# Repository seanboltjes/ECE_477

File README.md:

# Swing Analysis (Team 13)
Swing Analyzer's code repo!

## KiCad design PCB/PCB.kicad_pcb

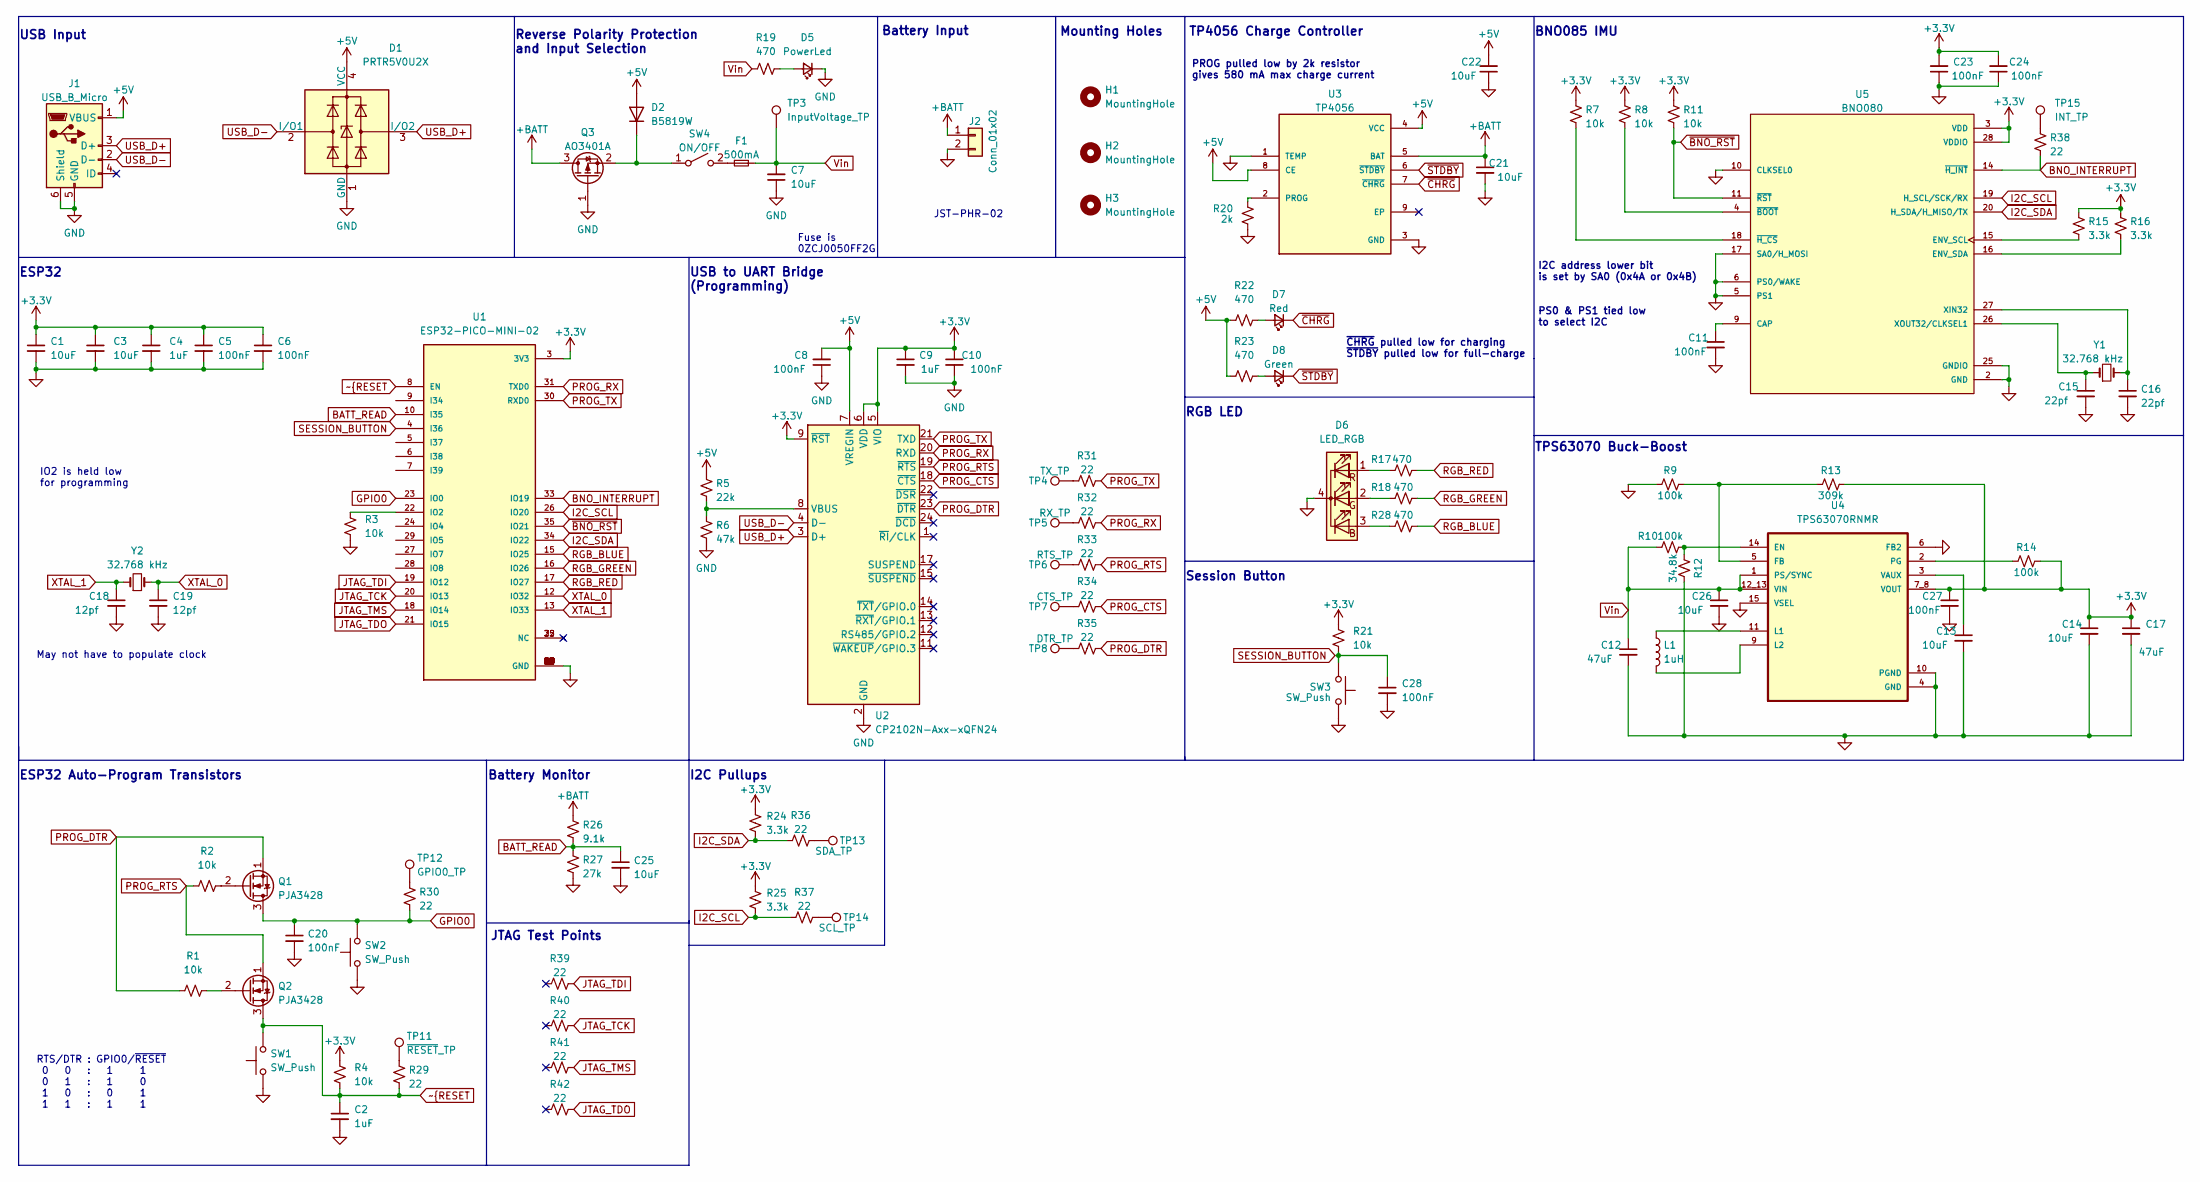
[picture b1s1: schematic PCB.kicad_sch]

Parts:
C1, C3, C13, C14, C25, C26: 10uF; C_0603_1608Metric
C2, C4, C9: 1uF; C_0603_1608Metric
C5, C6, C8, C10, C11, C20, C23, C24, C27, C28: 100nF; C_0603_1608Metric
C7, C21, C22: 10uF; C_1206_3216Metric
C12: 47uF; C_1206_3216Metric_Pad1.33x1.80mm_HandSolder
C15, C16: 22pf; C_0603_1608Metric
C17: 47uF; C_1206_3216Metric
C18, C19: 12pf; C_0603_1608Metric
D1: PRTR5V0U2X; SOT-143
D2: B5819W; D_1206_3216Metric
D5: PowerLed; LED_0805_2012Metric_Pad1.15x1.40mm_HandSolder
D6: LED_RGB; LED_D5.0mm-4_RGB
D7: Red; LED_0805_2012Metric_Pad1.15x1.40mm_HandSolder
D8: Green; LED_0805_2012Metric_Pad1.15x1.40mm_HandSolder
F1: 500mA; RESC3216X125N
H1, H2, H3: MountingHole; MountingHole_2.2mm_M2_Pad_Via
J1: USB_B_Micro; USB_Micro-B_Molex_47346-0001
J2: Conn_01x02; JST_PHR-2
L1: 1uH; IHLP1212BZER1R0M11
Q1, Q2: PJA3428; SC-82AA_Handsoldering
Q3: AO3401A; SOT-23
R1, R2, R3, R4, R7, R8, R11, R21: 10k; R_0603_1608Metric
R5: 22k; R_0603_1608Metric
R6: 47k; R_0603_1608Metric
R9, R10, R14: 100k; R_0603_1608Metric
R12: 34.8k; R_0603_1608Metric
R13: 309k; R_0603_1608Metric
R15, R16, R24, R25: 3.3k; R_0603_1608Metric
R17, R18, R19, R22, R23, R28: 470; R_0603_1608Metric
R20: 2k; R_0603_1608Metric
R26: 9.1k; R_0603_1608Metric
R27: 27k; R_0603_1608Metric
R29, R30, R31, R32, R33, R34, R35, R36, R37, R38, R39, R40, R41, R42: 22; R_0603_1608Metric
SW1, SW2: SW_Push; SW_Push_1P1T_NO_Vertical_Wuerth_434133025816
SW3: SW_Push; SW_Tactile_SPST_Angled_PTS645Vx58-2LFS
SW4: ON/OFF; CUS-12TB
TP3: InputVoltage_TP; TestPoint_Pad_D1.0mm
TP4: TX_TP; TestPoint_Pad_D1.0mm
TP5: RX_TP; TestPoint_Pad_D1.0mm
TP6: RTS_TP; TestPoint_Pad_D1.0mm
TP7: CTS_TP; TestPoint_Pad_D1.0mm
TP8: DTR_TP; TestPoint_Pad_D1.0mm
TP11: ~{RESET}_TP; TestPoint_Pad_D1.0mm
TP12: GPIO0_TP; TestPoint_Pad_D1.0mm
TP13: SDA_TP; TestPoint_Pad_D1.0mm
TP14: SCL_TP; TestPoint_Pad_D1.0mm
TP15: INT_TP; TestPoint_Pad_D1.0mm
U1: ESP32-PICO-MINI-02; MODULE_ESP32-PICO-MINI-02; PARTREV v1.0
U2: CP2102N-Axx-xQFN24; QFN-24-1EP_4x4mm_P0.5mm_EP2.6x2.6mm
U3: TP4056; SOP127P600X175-9N
U4: TPS63070RNMR; VREG_TPS63070RNMR
U5: BNO080; IC_BNO080; PARTREV 1.6
Y1, Y2: 32.768 kHz; Crystal_SMD_EuroQuartz_EQ161-2Pin_3.2x1.5mm

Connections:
+3.3V: C1.1, C3.1, C4.1, C5.1, C6.1, C9.1, C10.1, C14.1, C17.1, C23.2, C24.2, C27.1, R4.1, R7.1, R8.1, R11.1, R13.1, R14.1, R15.1, R16.1, R21.1, R24.1, R25.1, U1.3 (3V3), U2.5 (VIO), U2.6 (VDD), U2.9 (~RST), U4.7_8 (VOUT), U5.3 (VDD), U5.28 (VDDIO)
+5V: C8.2, C22.2, D1.4 (VCC), D2.2 (A), J1.1 (VBUS), R5.1, R22.1, R23.1, U2.7 (VREGIN), U3.4 (VCC), U3.8 (CE)
+BATT: C21.1, J2.1, Q3.3 (D), R26.1, U3.5 (BAT)
BATT_READ: C25.1, R26.2, R27.1, U1.10 (I35)
BNO_INTERRUPT: R38.1, U1.33 (IO19), U5.14 (~H_INT)
GND: C1.2, C2.2, C3.2, C4.2, C5.2, C6.2, C7.1, C8.1, C9.2, C10.2, C11.2, C12.2, C13.2, C14.2, C15.2, C16.2, C17.2, C18.2, C19.2, C20.2, C21.2, C22.1, C23.1, C24.1, C25.2, C26.2, C27.2, C28.2, D1.1 (GND), D5.1 (K), D6.4 (K), J1.5 (GND), J1.6 (Shield), J2.2, Q3.1 (G), R3.1, R6.2, R9.2, R12.1, R20.1, R27.2, SW1.1, SW2.1, SW3.2, U1.1 (GND), U1.2 (GND), U1.11 (GND), U1.14 (GND), U1.36 (GND), U1.37 (GND), U1.38 (GND), U1.39 (GND), U1.40 (GND), U1.41 (GND), U1.42 (GND), U1.43 (GND), U1.44 (GND), U1.45 (GND), U1.46 (GND), U1.47 (GND), U1.48 (GND), U1.49 (GND), U1.50 (GND), U1.51 (GND), U1.52 (GND), U1.53 (GND), U1.54 (GND), U1.55 (GND), U1.56 (GND), U1.57 (GND), U1.58 (GND), U1.59 (GND), U1.60 (GND), U1.61 (GND), U2.2 (GND), U2.25 (GND), U3.1 (TEMP), U3.3 (GND), U4.4 (GND), U4.6 (FB2), U4.10 (PGND), U4.15 (VSEL), U5.2 (GND), U5.5 (PS1), U5.6 (PS0/WAKE), U5.10 (CLKSEL0), U5.17 (SA0/H_MOSI), U5.25 (GNDIO)
GPIO0: C20.1, Q1.3 (D), R30.2, SW2.2, U1.23 (IO0)
I2C_SCL: R25.2, R37.1, U1.26 (IO20), U5.19 (H_SCL/SCK/RX)
I2C_SDA: R24.2, R36.1, U1.34 (IO22), U5.20 (H_SDA/H_MISO/TX)
JTAG_TCK: R40.2, U1.20 (IO13)
JTAG_TDI: R39.2, U1.19 (IO12)
JTAG_TDO: R42.2, U1.21 (IO15)
JTAG_TMS: R41.2, U1.18 (IO14)
unnamed: C11.1, U5.9 (CAP)
unnamed: C13.1, U4.3 (VAUX)
unnamed: C15.1, U5.26 (XOUT32/CLKSEL1), Y1.1
unnamed: C16.1, U5.27 (XIN32), Y1.2
unnamed: D2.1 (K), Q3.2 (S), SW4.1 (A)
unnamed: D5.2 (A), R19.2
unnamed: D6.1 (RA), R17.1
unnamed: D6.2 (GA), R18.1
unnamed: D6.3 (BA), R28.1
unnamed: D7.2 (A), R22.2
unnamed: D8.2 (A), R23.2
unnamed: F1.1, SW4.2 (B)
unnamed: L1.1, U4.11 (L1)
unnamed: L1.2, U4.9 (L2)
unnamed: Q1.2 (G), R2.2
unnamed: Q2.2 (G), R1.2
unnamed: R3.2, U1.22 (IO2)
unnamed: R5.2, R6.1, U2.8 (VBUS)
unnamed: R7.2, U5.18 (~H_CS)
unnamed: R8.2, U5.4 (~BOOT)
unnamed: R10.2, R12.2, U4.14 (EN)
unnamed: R9.1, R13.2, U4.5 (FB)
unnamed: R14.2, U4.2 (PG)
unnamed: R15.2, U5.15 (ENV_SCL)
unnamed: R16.2, U5.16 (ENV_SDA)
unnamed: R20.2, U3.2 (PROG)
unnamed: R29.1, TP11.1
unnamed: R30.1, TP12.1
unnamed: R31.1, TP4.1
unnamed: R32.1, TP5.1
unnamed: R33.1, TP6.1
unnamed: R34.1, TP7.1
unnamed: R35.1, TP8.1
unnamed: R36.2, TP13.1
unnamed: R37.2, TP14.1
unnamed: R38.2, TP15.1
PROG_CTS: R34.2, U2.18 (~CTS)
PROG_DTR: Q1.1 (S), R1.1, R35.2, U2.23 (~DTR)
PROG_RTS: Q2.1 (S), R2.1, R33.2, U2.19 (~RTS)
PROG_RX: R32.2, U1.31 (TXD0), U2.20 (RXD)
PROG_TX: R31.2, U1.30 (RXD0), U2.21 (TXD)
RGB_BLUE: R28.2, U1.15 (IO25)
RGB_GREEN: R18.2, U1.16 (IO26)
RGB_RED: R17.2, U1.17 (IO27)
SESSION_BUTTON: C28.1, R21.2, SW3.1, U1.4 (I36)
USB_D+: D1.3 (I/O2), J1.3 (D+), U2.3 (D+)
USB_D-: D1.2 (I/O1), J1.2 (D-), U2.4 (D-)
Vin: C7.2, C12.1, C26.1, F1.2, R10.1, R19.1, TP3.1, U4.1 (PS/SYNC), U4.12_13 (VIN)
XTAL_0: C19.1, U1.12 (IO32), Y2.2
XTAL_1: C18.1, U1.13 (IO33), Y2.1
~BNO_RST: R11.2, U1.35 (IO21), U5.11 (~RST)
~CHRG: D7.1 (K), U3.7 (~CHRG)
~RESET: C2.1, Q2.3 (D), R4.2, R29.2, SW1.2, U1.8 (EN)
~STDBY: D8.1 (K), U3.6 (~STDBY)

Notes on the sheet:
RTS/DTR : GPIO0/~{RESET} 0 0 : 1 1 0 1 : 1 0 1 0 : 0 1 1 1 : 1 1
PROG pulled low by 2k resistor gives 580 mA max charge current
May not have to populate clock
BNO085 IMU
USB Input
ESP32
IO2 is held low for programming
Mounting Holes
Reverse Polarity Protection and Input Selection
JST-PHR-02
I2C address lower bit is set by SA0 (0x4A or 0x4B)
Fuse is 0ZCJ0050FF2G
Battery Monitor
USB to UART Bridge (Programming)
JTAG Test Points
I2C Pullups
Session Button
~{CHRG} pulled low for charging ~{STDBY} pulled low for full-charge
ESP32 Auto-Program Transistors
RGB LED
Battery Input
PS0 & PS1 tied low to select I2C
TP4056 Charge Controller
TPS63070 Buck-Boost

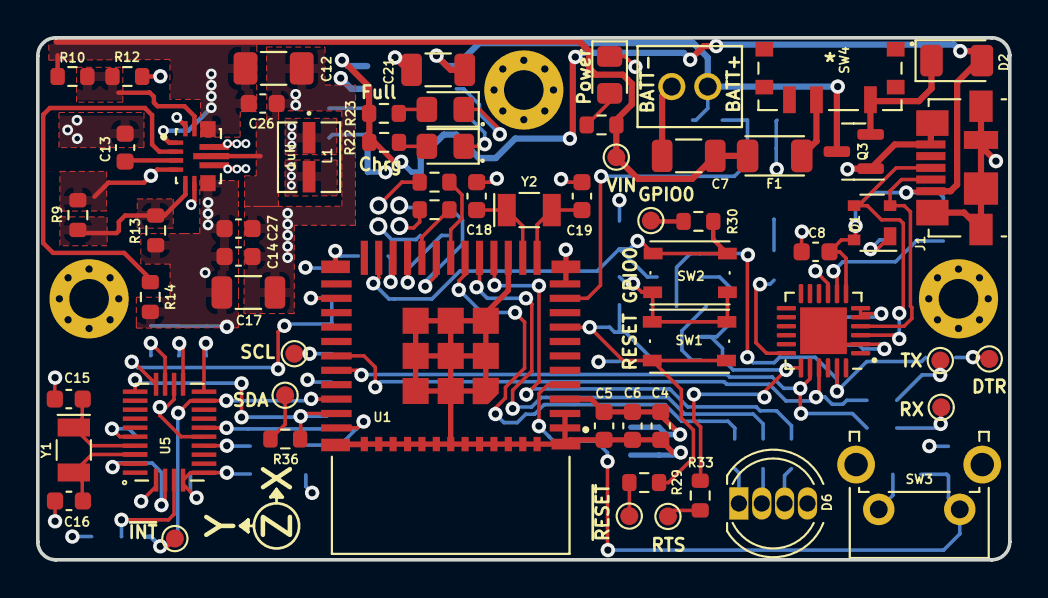
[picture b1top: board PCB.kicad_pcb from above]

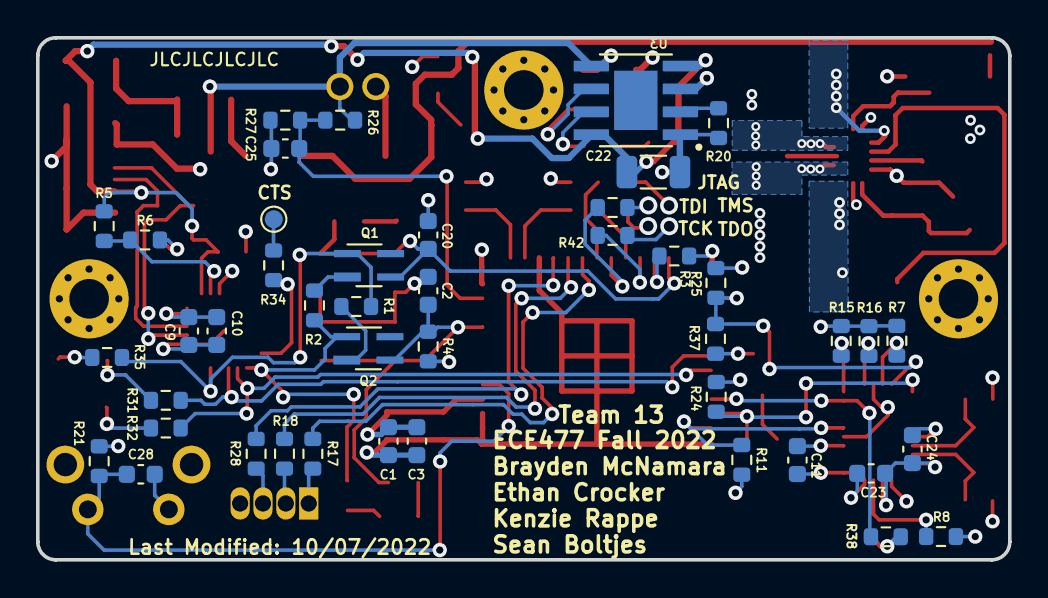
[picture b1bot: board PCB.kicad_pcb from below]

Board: 4 copper layers, 54.0 x 29.0 mm, 108 parts (44 on the bottom side), 67 nets.

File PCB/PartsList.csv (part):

Source:,C:\Users\seanb\Downloads\PCB-Team13\PCB-Team13\PCB.kicad_sch,,,,,,,,,
Date:,10/17/2022 13:33,,,,,,,,,
Tool:,Eeschema (6.0.7),,,,,,,,,
Generator:,C:\Program Files\KiCad\6.0\bin\scripting\plugins/bom_csv_grouped_by_value.py,,,,,,,,,
Component Count:,108,,,,,,,,,
,,,,,,,,,,
Individual Components:,,,,,,,,,,
,,,,,,,,,,
Item,Qty,Reference(s),Value,LibPart,Footprint,Datasheet,MANUFACTURER,MAXIMUM_PACKAGE_HEIGHT,PARTREV,STANDARD
,,C1,10uF,Device:C_Small,Capacitor_SMD:C_0603_1608Metric,~,,,,
,,C2,1uF,Device:C_Small,Capacitor_SMD:C_0603_1608Metric,~,,,,
,,C3,10uF,Device:C_Small,Capacitor_SMD:C_0603_1608Metric,~,,,,
,,C4,1uF,Device:C_Small,Capacitor_SMD:C_0603_1608Metric,~,,,,
,,C5,100nF,Device:C_Small,Capacitor_SMD:C_0603_1608Metric,~,,,,
,,C6,100nF,Device:C_Small,Capacitor_SMD:C_0603_1608Metric,~,,,,
,,C7,10uF,Device:C_Small,Capacitor_SMD:C_1206_3216Metric,~,,,,
,,C8,100nF,Device:C_Small,Capacitor_SMD:C_0603_1608Metric,~,,,,
,,C9,1uF,Device:C_Small,Capacitor_SMD:C_0603_1608Metric,~,,,,
,,C10,100nF,Device:C_Small,Capacitor_SMD:C_0603_1608Metric,~,,,,
,,C11,100nF,Device:C_Small,Capacitor_SMD:C_0603_1608Metric,~,,,,
,,C12,47uF,Device:C_Small,Capacitor_SMD:C_1206_3216Metric_Pad1.33x1.80mm_HandSolder,~,,,,
,,C13,10uF,Device:C_Small,Capacitor_SMD:C_0603_1608Metric,~,,,,
,,C14,10uF,Device:C_Small,Capacitor_SMD:C_0603_1608Metric,~,,,,
,,C15,12pf,Device:C_Small,Capacitor_SMD:C_0603_1608Metric,~,,,,
,,C16,12pf,Device:C_Small,Capacitor_SMD:C_0603_1608Metric,~,,,,
,,C17,47uF,Device:C_Small,Capacitor_SMD:C_1206_3216Metric,~,,,,
,,C18,12pf,Device:C_Small,Capacitor_SMD:C_0603_1608Metric,~,,,,
,,C19,12pf,Device:C_Small,Capacitor_SMD:C_0603_1608Metric,~,,,,
,,C20,100nF,Device:C_Small,Capacitor_SMD:C_0603_1608Metric,~,,,,
,,C21,10uF,Device:C_Small,Capacitor_SMD:C_1206_3216Metric,~,,,,
,,C22,10uF,Device:C_Small,Capacitor_SMD:C_1206_3216Metric,~,,,,
,,C23,100nF,Device:C_Small,Capacitor_SMD:C_0603_1608Metric,~,,,,
,,C24,100nF,Device:C_Small,Capacitor_SMD:C_0603_1608Metric,~,,,,
,,C25,10uF,Device:C_Small,Capacitor_SMD:C_0603_1608Metric,~,,,,
,,C26,10uF,Device:C_Small,Capacitor_SMD:C_0603_1608Metric,~,,,,
,,C27,100nF,Device:C_Small,Capacitor_SMD:C_0603_1608Metric,~,,,,
,,C28,100nF,Device:C_Small,Capacitor_SMD:C_0603_1608Metric,~,,,,
,,D1,PRTR5V0U2X,Power_Protection:PRTR5V0U2X,Package_TO_SOT_SMD:SOT-143,https://assets.nexperia.com/documents/data-sheet/PRTR5V0U2X.pdf,,,,
,,D2,1N4148,Diode:1N4148,Diode_SMD:D_1206_3216Metric,https://assets.nexperia.com/documents/data-sheet/1N4148_1N4448.pdf,,,,
,,D5,PowerLed,Device:LED_Small,LED_SMD:LED_0805_2012Metric_Pad1.15x1.40mm_HandSolder,~,,,,
,,D6,LED_RGB,Device:LED_RGBK,LED_THT:LED_D5.0mm-4_RGB,~,,,,
,,D7,Red,Device:LED_Small,LED_SMD:LED_0805_2012Metric_Pad1.15x1.40mm_HandSolder,~,,,,
,,D8,Green,Device:LED_Small,LED_SMD:LED_0805_2012Metric_Pad1.15x1.40mm_HandSolder,~,,,,
,,F1,500mA,Device:Fuse_Small,0ZCJ0050FF2G:RESC3216X125N,~,,,,
,,H1,MountingHole,Mechanical:MountingHole,MountingHole:MountingHole_2.2mm_M2_Pad_Via,~,,,,
,,H2,MountingHole,Mechanical:MountingHole,MountingHole:MountingHole_2.2mm_M2_Pad_Via,~,,,,
,,H3,MountingHole,Mechanical:MountingHole,MountingHole:MountingHole_2.2mm_M2_Pad_Via,~,,,,
,,J1,USB_B_Micro,Connector:USB_B_Micro,Connector_USB:USB_Micro-B_Molex_47346-0001,~,,,,
,,J2,Conn_01x02,Connector_Generic:Conn_01x02,PHR-2:JST_PHR-2,~,,,,
,,L1,L,Device:L,inductor:IHLP1212BZERR56M11,~,,,,
,,Q1,PJA3428,Transistor_FET:2N7000,Package_TO_SOT_SMD:SC-82AA_Handsoldering,https://www.vishay.com/docs/70226/70226.pdf,,,,
,,Q2,PJA3428,Transistor_FET:2N7000,Package_TO_SOT_SMD:SC-82AA_Handsoldering,https://www.vishay.com/docs/70226/70226.pdf,,,,
,,Q3,AO3401A,Transistor_FET:AO3401A,Package_TO_SOT_SMD:SOT-23,http://www.aosmd.com/pdfs/datasheet/AO3401A.pdf,,,,
,,R1,10k,Device:R_Small_US,Resistor_SMD:R_0603_1608Metric,~,,,,
,,R2,10k,Device:R_Small_US,Resistor_SMD:R_0603_1608Metric,~,,,,
,,R3,10k,Device:R_Small_US,Resistor_SMD:R_0603_1608Metric,~,,,,
,,R4,10k,Device:R_Small_US,Resistor_SMD:R_0603_1608Metric,~,,,,
,,R5,22k,Device:R_Small_US,Resistor_SMD:R_0603_1608Metric,~,,,,
,,R6,47k,Device:R_Small_US,Resistor_SMD:R_0603_1608Metric,~,,,,
,,R7,10k,Device:R_Small_US,Resistor_SMD:R_0603_1608Metric,~,,,,
,,R8,10k,Device:R_Small_US,Resistor_SMD:R_0603_1608Metric,~,,,,
,,R9,100k,Device:R_Small_US,Resistor_SMD:R_0603_1608Metric,~,,,,
,,R10,100k,Device:R_Small_US,Resistor_SMD:R_0603_1608Metric,~,,,,
,,R11,10k,Device:R_Small_US,Resistor_SMD:R_0603_1608Metric,~,,,,
,,R12,34.8k,Device:R_Small_US,Resistor_SMD:R_0603_1608Metric,~,,,,
,,R13,309k,Device:R_Small_US,Resistor_SMD:R_0603_1608Metric,~,,,,
,,R14,100k,Device:R_Small_US,Resistor_SMD:R_0603_1608Metric,~,,,,
,,R15,3.3k,Device:R_Small_US,Resistor_SMD:R_0603_1608Metric,~,,,,
,,R16,3.3k,Device:R_Small_US,Resistor_SMD:R_0603_1608Metric,~,,,,
,,R17,470,Device:R_Small_US,Resistor_SMD:R_0603_1608Metric,~,,,,
,,R18,470,Device:R_Small_US,Resistor_SMD:R_0603_1608Metric,~,,,,
,,R19,470,Device:R_Small_US,Resistor_SMD:R_0603_1608Metric,~,,,,
,,R20,2k,Device:R_Small_US,Resistor_SMD:R_0603_1608Metric,~,,,,
,,R21,10k,Device:R_Small_US,Resistor_SMD:R_0603_1608Metric,~,,,,
,,R22,470,Device:R_Small_US,Resistor_SMD:R_0603_1608Metric,~,,,,
,,R23,470,Device:R_Small_US,Resistor_SMD:R_0603_1608Metric,~,,,,
,,R24,3.3k,Device:R_Small_US,Resistor_SMD:R_0603_1608Metric,~,,,,
,,R25,3.3k,Device:R_Small_US,Resistor_SMD:R_0603_1608Metric,~,,,,
,,R26,9.1k,Device:R_Small_US,Resistor_SMD:R_0603_1608Metric,~,,,,
,,R27,27k,Device:R_Small_US,Resistor_SMD:R_0603_1608Metric,~,,,,
,,R28,470,Device:R_Small_US,Resistor_SMD:R_0603_1608Metric,~,,,,
,,R29,22,Device:R_Small_US,Resistor_SMD:R_0603_1608Metric,~,,,,
,,R30,22,Device:R_Small_US,Resistor_SMD:R_0603_1608Metric,~,,,,
,,R31,22,Device:R_Small_US,Resistor_SMD:R_0603_1608Metric,~,,,,
,,R32,22,Device:R_Small_US,Resistor_SMD:R_0603_1608Metric,~,,,,
,,R33,22,Device:R_Small_US,Resistor_SMD:R_0603_1608Metric,~,,,,
,,R34,22,Device:R_Small_US,Resistor_SMD:R_0603_1608Metric,~,,,,
,,R35,22,Device:R_Small_US,Resistor_SMD:R_0603_1608Metric,~,,,,
,,R36,22,Device:R_Small_US,Resistor_SMD:R_0603_1608Metric,~,,,,
,,R37,22,Device:R_Small_US,Resistor_SMD:R_0603_1608Metric,~,,,,
,,R38,22,Device:R_Small_US,Resistor_SMD:R_0603_1608Metric,~,,,,
,,R39,22,Device:R_Small_US,Resistor_SMD:R_0603_1608Metric,~,,,,
,,R40,22,Device:R_Small_US,Resistor_SMD:R_0603_1608Metric,~,,,,
,,R41,22,Device:R_Small_US,Resistor_SMD:R_0603_1608Metric,~,,,,
,,R42,22,Device:R_Small_US,Resistor_SMD:R_0603_1608Metric,~,,,,
,,SW1,SW_Push,Switch:SW_Push,Button_Switch_SMD:SW_Push_1P1T_NO_Vertical_Wuerth_434133025816,~,,,,
,,SW2,SW_Push,Switch:SW_Push,Button_Switch_SMD:SW_Push_1P1T_NO_Vertical_Wuerth_434133025816,~,,,,
,,SW3,SW_Push,Switch:SW_Push,Button_Switch_THT:SW_Tactile_SPST_Angled_PTS645Vx58-2LFS,~,,,,
,,SW4,ON/OFF,Switch:SW_SPST,footprints:CUS-12TB,~,,,,
,,TP3,InputVoltage_TP,Connector:TestPoint,TestPoint:TestPoint_Pad_D1.0mm,~,,,,
,,TP4,TX_TP,Connector:TestPoint,TestPoint:TestPoint_Pad_D1.0mm,~,,,,
,,TP5,RX_TP,Connector:TestPoint,TestPoint:TestPoint_Pad_D1.0mm,~,,,,
,,TP6,RTS_TP,Connector:TestPoint,TestPoint:TestPoint_Pad_D1.0mm,~,,,,
,,TP7,CTS_TP,Connector:TestPoint,TestPoint:TestPoint_Pad_D1.0mm,~,,,,
,,TP8,DTR_TP,Connector:TestPoint,TestPoint:TestPoint_Pad_D1.0mm,~,,,,
,,TP11,~{RESET}_TP,Connector:TestPoint,TestPoint:TestPoint_Pad_D1.0mm,~,,,,
,,TP12,GPIO0_TP,Connector:TestPoint,TestPoint:TestPoint_Pad_D1.0mm,~,,,,
,,TP13,SDA_TP,Connector:TestPoint,TestPoint:TestPoint_Pad_D1.0mm,~,,,,
,,TP14,SCL_TP,Connector:TestPoint,TestPoint:TestPoint_Pad_D1.0mm,~,,,,
,,TP15,INT_TP,Connector:TestPoint,TestPoint:TestPoint_Pad_D1.0mm,~,,,,
,,U1,ESP32-PICO-MINI-02,ESP32-PICO-MINI-02:ESP32-PICO-MINI-02,ESP32:MODULE_ESP32-PICO-MINI-02,,Espressif,2.55mm,v1.0,Manufacturer Recommendations
,,U2,CP2102N-Axx-xQFN24,Interface_USB:CP2102N-Axx-xQFN24,Package_DFN_QFN:QFN-24-1EP_4x4mm_P0.5mm_EP2.6x2.6mm,https://www.silabs.com/documents/public/data-sheets/cp2102n-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,,,,
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
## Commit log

2022-08-30 Added testing and progress
2022-08-30 clean up pde setup
2022-09-05 test the 6 DOF Orientation
2022-09-06 first attempt dead reckoning - huge error margin tho
2022-09-06 zero correction
2022-09-06 better code
2022-09-06 added gifs for demo
2022-09-06 YEEESSSS!!!!!
2022-09-08 Refactor everything and get position visualization working
2022-09-08 in lab demo
2022-09-13 bno test
2022-09-13 lab progress
2022-09-13 working bno
2022-09-16 LEEETSSS GOOOO DEAD RECKONING WORKS (kinda)
2022-09-16 PCB creation
2022-09-16 bno085 schematic done
2022-09-20 attempt (x axis is weird)
2022-09-21 working?
2022-09-21 buck-boost schematic added
2022-09-21 added micro and voltage input schematics
2022-09-23 commit me
2022-09-23 pcb edits
2022-09-23 pcb update (transistors)
2022-09-26 edge cut improvement and general placements for mechanical design
2022-09-26 post edit cache
2022-09-27 progress on tp4056
2022-09-27 buck-boost schem vals
2022-09-27 bb schem changes
2022-09-27 added resistor
2022-09-27 more tp4056 progress
2022-09-29 most schematics done
2022-09-29 more footprints!
2022-09-30 huuuuge progress
2022-09-30 more placements
2022-09-30 placements for everything besides buck/boost
2022-09-30 starting routing
2022-09-30 fix power plane issue and more routing
2022-10-01 redid battery voltage measure
2022-10-01 buck-boost schem
    old schem deleted new one started
2022-10-03 more routin'
2022-10-03 almost done routing
2022-10-03 main routing finished
2022-10-03 component references added
2022-10-03 label btns and tps
2022-10-04 silky touch ups
2022-10-04 final (hopefully) buck-boost schem
2022-10-04 buck-boost
2022-10-04 buck-boost delete
2022-10-04 buck-boost pcb
    buck-boost added to pcb
2022-10-04 bb_check
2022-10-05 updates based on in lab feedback and errors
2022-10-05 update the very silky screen
2022-10-06 update power connector and silkscreen
2022-10-07 buck-boost pcb changes
2022-10-07 huuuge rerouting and replacement. Added ESD protection resistors
2022-10-07 add JTAG support
2022-10-07 minor changes
2022-10-11 buck-boost pcb
    layout updated
2022-10-12 buck-boost layout
    changed to layout from TI Web bench
2022-10-12 buck-boost edits
2022-10-12 update pcb with Vin input
2022-10-12 added step models + footprint updates
2022-10-13 buck-boost routing 1
2022-10-13 good luck
2022-10-13 update
    routing and planes
2022-10-13 buck/boost
2022-10-13 buck/boost more progress
2022-10-13 button update
2022-10-14 fix silkscreen issues before design review
2022-10-14 added exclusion zones to oscillators
2022-10-17 parts list start
2022-10-18 final changes
2022-10-18 schem edits
2022-10-18 parts list update
2022-10-18 final PCB push
2022-10-18 better gerbers
2022-10-18 100nF
2022-10-19 THIS WAS THE PCB THAT WAS ORDERED
2022-10-20 working bluetooth stuff
2022-10-20 Revert "working bluetooth stuff"
    This reverts commit 34ef5b96a591997f13d62c6b10f4f82ffc883183.
